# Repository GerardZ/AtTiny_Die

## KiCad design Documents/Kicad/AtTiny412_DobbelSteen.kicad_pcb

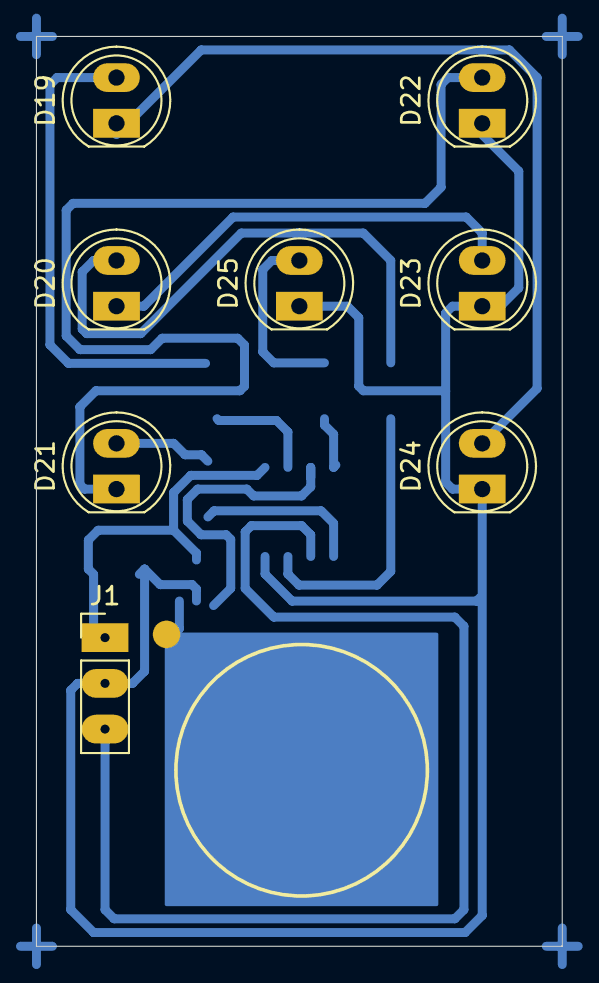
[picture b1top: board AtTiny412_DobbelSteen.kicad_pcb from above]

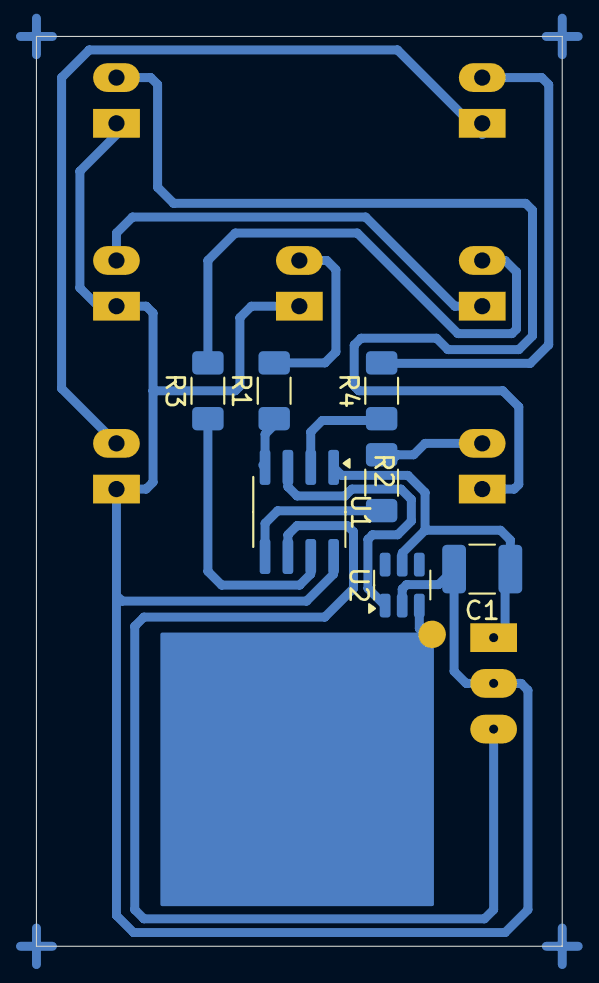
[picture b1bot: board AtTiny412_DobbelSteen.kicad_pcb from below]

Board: 2 copper layers, 29.2 x 50.5 mm, 16 parts (8 on the bottom side), 16 nets.

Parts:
C1: 100n; C_1210_3225Metric_Pad1.33x2.70mm_HandSolder
D19, D20, D21, D22, D23, D24, D25: Red; LED_D5.0mm
J1: Conn_01x03_Pin; PinHeader_1x03_P2.54mm_Vertical
R1, R2, R3, R4: R 270; R_1206_3216Metric_Pad1.30x1.75mm_HandSolder
U1: ATtiny412-SS; SOIC-8_3.9x4.9mm_P1.27mm
U2: SOT-23-6
U3: TTP226-PAD

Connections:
+5V: C1.1, J1.1, U1.1 (VCC), U2.5 (Vdd)
GND: C1.2, D22.1 (K), D23.1 (K), D24.1 (K), D25.1 (K), J1.2, U1.8 (GND), U2.2 (Vss)
unnamed: D19.2 (A), R4.2
unnamed: D19.1 (K), D24.2 (A)
unnamed: D20.2 (A), R3.2
unnamed: D20.1 (K), D23.2 (A)
unnamed: D21.2 (A), R2.2
unnamed: D21.1 (K), D22.2 (A)
unnamed: D25.2 (A), R1.2
unnamed: J1.3, U1.6 (~RESET/PA0)
unnamed: R1.1, U1.4 (PA1)
unnamed: R2.1, U1.5 (PA2)
unnamed: R3.1, U1.7 (PA3)
unnamed: R4.1, U1.2 (PA6)
unnamed: U1.3 (PA7), U2.1 (Q)
unnamed: U2.3 (In), U3.1 (sense___)

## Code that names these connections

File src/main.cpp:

#include <Arduino.h>

#define ledsA PIN_PA6
#define ledsB PIN_PA3
#define ledsC PIN_PA2
#define ledD PIN_PA1
#define touch PIN_PA7

const int16_t countValue[10] PROGMEM = { // organized in value, step, where value is mSec, step number of step to get to the next value
    10, 200,
    50, 10,
    100, 5,
    500, 1};

void setup()
{
  pinMode(ledsA, OUTPUT);
  pinMode(ledsB, OUTPUT);
  pinMode(ledsC, OUTPUT);
  pinMode(ledD, OUTPUT);
  pinMode(touch, INPUT);
}

void allOff()
{
  digitalWrite(ledsA, 0);
  digitalWrite(ledsB, 0);
  digitalWrite(ledsC, 0);
  digitalWrite(ledD, 0);
}

void setValue(uint8_t value)
{
  allOff();
  switch (value)
  {
  case 1:
    digitalWrite(ledD, 1);
    return;
  case 2:
    digitalWrite(ledsA, 1);
    return;
  case 3:
    digitalWrite(ledsC, 1);
    digitalWrite(ledD, 1);
    return;
  case 4:
    digitalWrite(ledsC, 1);
    digitalWrite(ledsA, 1);
    return;
  case 5:
    digitalWrite(ledsC, 1);
    digitalWrite(ledsA, 1);
    digitalWrite(ledD, 1);
    return;
  case 6:
    digitalWrite(ledsC, 1);
    digitalWrite(ledsB, 1);
    digitalWrite(ledsA, 1);
    return;
  }
}

uint16_t wait = 150;
bool WaitLoop(bool init = false)
{
  if (init)
    wait = 150;

  uint16_t delayValue = 1200 / wait--;
  delay(delayValue);

  if (!wait)
    return true;
  return false;
}

uint16_t lfsr = 0x3CE1; // seed
uint16_t bit;           // Holds the feedback bit

uint16_t lfsr_next() // pseudo random lfsr 16bit
{
  bit = ((lfsr >> 0) ^ (lfsr >> 2) ^ (lfsr >> 3) ^ (lfsr >> 5)) & 1;
  lfsr = (lfsr >> 1) | (bit << 15);
  return lfsr;
}

uint8_t value;
void loop()
{
  while (!digitalRead(touch)) // hold while not pressed
  {
    delay(10);
    lfsr_next();  // keep randomizing...
  }

  while (digitalRead(touch)) // touch pressed...
  {
    value = lfsr_next() % 6 + 1;
    setValue(value);
  }

  WaitLoop(true); // touch released, animate runout
  while (!WaitLoop())
  {
    value++;
    if (value > 6)
      value = 1;
    setValue(value);
  }

  for (uint8_t count = 0; count < 6; count++) // blink value
  {
    delay(200);
    setValue(0);
    delay(200);
    setValue(value);
  }

  delay(3000);    // holdoff 3 secs
}

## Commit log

2024-12-01 init, all ready
